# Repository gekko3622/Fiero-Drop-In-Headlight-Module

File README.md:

# 1987-1988 Pontiac Fiero OEM Drop-In Headlight Motor Controller
**PCB Designed by Ryan Blanchard 4.2024**\
**Based On A Project by WalkerTexan**\
**FOR NON-COMMERCIAL USE ONLY.**

**Important:** Please pay attention to the Bill of Materials (BOM). Some components have been changed from my previous designs.\
**This PCB MUST be fabricated with 2 Oz Outer Copper Weight for power handling and safety.**

## Intro

This is a PCB implementation of WalkerTexan's "Fiero Headlight Controller" project.\
I started this project after getting frustrated with the cost and questionable reliability of used modules.\
While there are new reproductions of the original module available, I found the cost to be too high.

After publishing my original PCB implementation, I was challenged to make it fit inside the original GM module's housing. Here it is.

## Repository Contents

**1. Arduino Program**
- WalkerTexan's code for the Arduino Nano.\
This MUST be programmed onto the Pro Micro for the module to function.

**2. Gerber Files (For Production)**
- These are the files that must be provided to a fabricator to produce a PCB.\
  **VERY IMPORTANT:** This PCB MUST be produced with 2 Oz outer copper weight in order to meet power handling requirements.\
  The provided gerber files will produce an identical copy of the PCB installed in my own car, just minus my logo.

  The Zip file can be directly submitted to a fabricator and contains all of the other individual files in this folder.

**3. KiCad Project Files**
- These are my full design schematic and PCB layout files. Use them for learning PCB design or to create your own custom version of the module.

  This project requires KiCad v8 or higher.

## Requirements
This project requires that you already have a fried 87-88 headlight module. (You're considering this project for a reason, right?)\
A Firebird or Corvette module of similar design can also be used.

- You will need to desolder and re-use the original 4 and 5 pin headers from your original module.
- The original module case will also be reused, but requires a single modification.

## Important Building Tips

**1. Arduino Pro Micro**

Due to the low clearance of the GM module casing, the Pro Micro must be installed lower on its pins than standard.\
It is also installed in a DIP socket to further reduce the mounting height.

My recommendation is to install the DIP socket first, then push the Pro Micro's pins into it.\
While installed, push down the plastic spacer, moving side to side until it's as flush as possible with the socket.

You can really see the difference in this side-by-side:

Once you've adjusted the pins for each side, place the Pro Micro onto the pins and solder it while socketed.

**2. Fuses**

I designed the module to directly solder in standard automotive mini fuses.\
For my own board, I used low profile mini fuses in order to avoid having to trim the fuse legs.

Regular mini fuses will work fine, just trim the legs after soldering.
  - 15 amps should be fine assuming your motors are in good shape.

**3. 4/5 Pin Original Header Pins**

The header pins must be installed slightly pulled out from the board to compensate for the added height of the relays.\
I tried my best to capture an image to demonstrate the needed spacing, but it's hard get a clear shot when assembled.

I found it easiest to install the pins one side at a time, getting them lined up right when installed into the housing.\
The holes for the headers are a pretty tight fit, so you should be able to position them fairly easily without them falling out.\
Once I was satisfied with the fitment, I lightly soldered a pin or two per side while still in the casing just to make sure the alignment was right.

**4. Modifying the Module Case**

The sole casing modification needed is to remove most of the plastic spacers from the back panel.\
The plastic is pretty soft, so I was able to grab and twist with vice grips to remove most of the material.

**You do not need to fully remove the spacers, just enough so the back panel can be re-installed without flexing.**\
**The round corner pieces do not need to be removed.**

Here's a comparison of an intact panel and my hastily trimmed panel. If you have the time, sanding them would give a more precise fit.

## Modifications to Original Source
1. Recreated the schematic diagram in KiCad.
2. Designed a PCB based on the schematic.
3. Added fuses and changed the power-on circuit to draw its power from the second 12V source.
4. Substituted the relays for a smaller part with higher current rating.
5. Adapted for compatibility with the original headlight module.

## Credits
The electrical schematic and Arduino code this project is based on were created by WalkerTexan.\
See his original project here: https://www.hackster.io/walkertexan/fiero-headlight-controller-8eaa4c

KiCad Schematic and PCB Layout/Design by Ryan Blanchard.

## License
This project is published under the Creative Commons Attribution-NonCommercial-ShareAlike 4.0 International license.\
Use of this project for commercial purposes is prohibited.

For full details, see the license file.

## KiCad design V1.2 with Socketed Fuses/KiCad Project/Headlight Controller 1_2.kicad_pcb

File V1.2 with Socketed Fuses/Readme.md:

V1.2 maintains the same BOM but adds socketed fuse holders.\
The specific holders I used are the micro fuse holders on this listing:\
https://www.aliexpress.us/item/2255800354773238.html

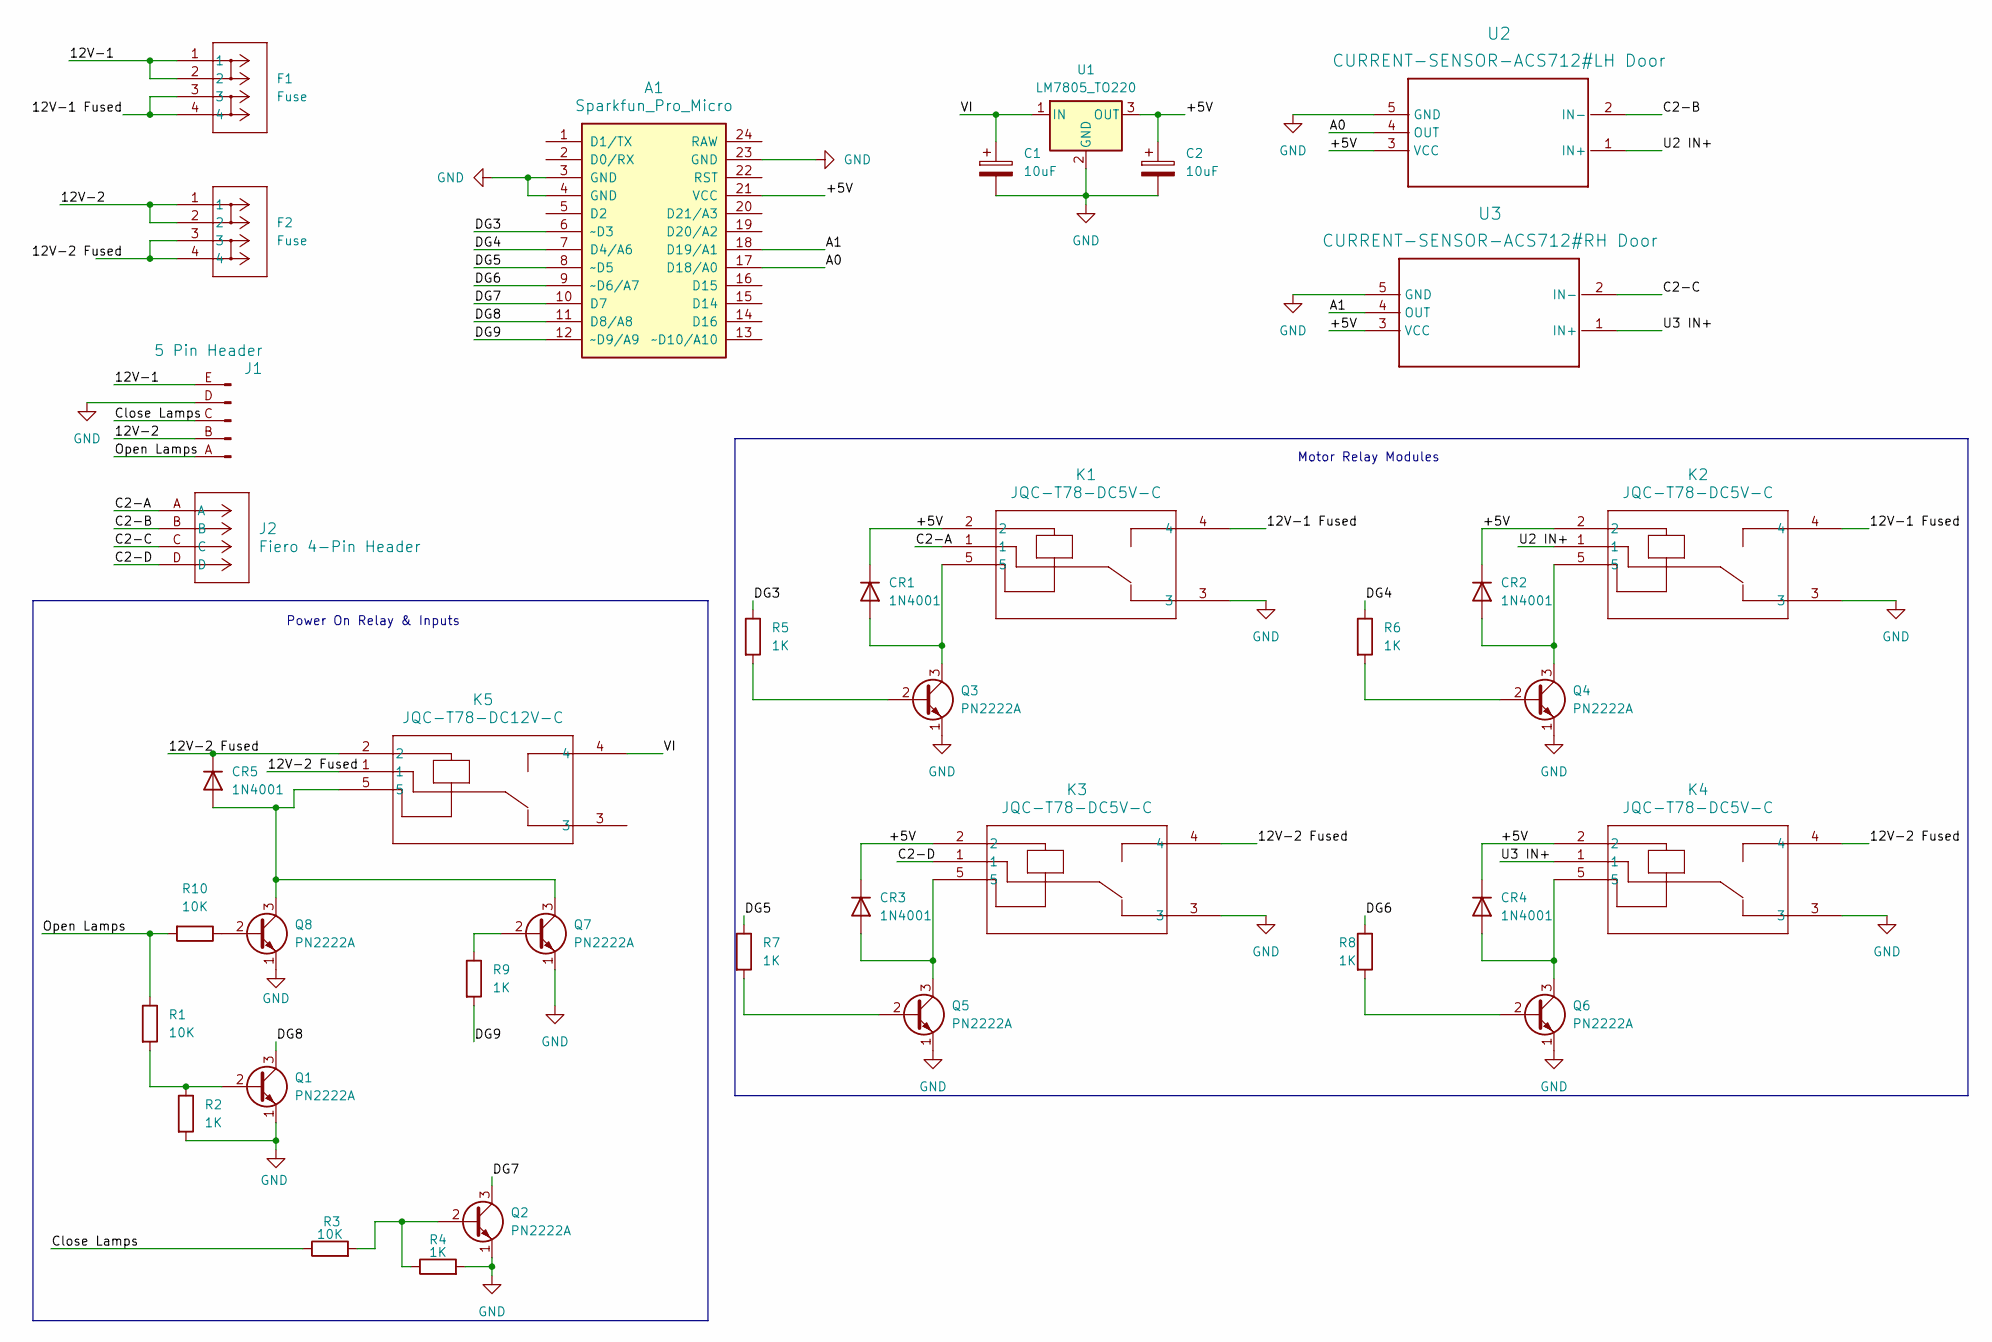
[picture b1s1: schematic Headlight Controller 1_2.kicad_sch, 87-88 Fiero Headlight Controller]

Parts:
A1: Sparkfun_Pro_Micro
C1, C2: 10uF; CAP-TH_BD5.0-P2.00-D0.8-FD
CR1, CR2, CR3, CR4, CR5: 1N4001; DIODE-1N4001
F1, F2: Fuse; LP-Mini Fuse Holder
J1: 5 Pin Header; Fiero Headlight Controller 5-Pin
J2: Fiero 4-Pin Header; Fiero Headlight Controller 4-Pin
K1, K2, K3, K4: JQC-T78-DC5V-C
K5: JQC-T78-DC12V-C; JQC-T78-DC5V-C
Q1, Q2, Q3, Q4, Q5, Q6, Q7, Q8: PN2222A; 2N2222A
R1, R3, R10: 10K; R_Axial_DIN0204_L3.6mm_D1.6mm_P7.62mm_Horizontal
R2, R4, R5, R6, R7, R8, R9: 1K; R_Axial_DIN0204_L3.6mm_D1.6mm_P7.62mm_Horizontal
U1: LM7805_TO220; L7805
U2: CURRENT-SENSOR-ACS712#LH Door; ACS712_A
U3: CURRENT-SENSOR-ACS712#RH Door; ACS712_A

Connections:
/12V-1: F1.1, F1.2, J1.E
/12V-1 Fused: F1.3, F1.4, K1.4, K2.4
/12V-2: F2.1, F2.2, J1.B
/12V-2 Fused: CR5.C (K), F2.3, F2.4, K3.4, K4.4, K5.1, K5.2
/+5V: A1.21 (VCC), C2.1, CR1.C (K), CR2.C (K), CR3.C (K), CR4.C (K), K1.2, K2.2, K3.2, K4.2, U1.3 (OUT), U2.3 (VCC), U3.3 (VCC)
/A0: A1.17 (D18/A0), U2.4 (OUT)
/A1: A1.18 (D19/A1), U3.4 (OUT)
/C2-A: J2.A, K1.1
/C2-B: J2.B, U2.2 (IN-)
/C2-C: J2.C, U3.2 (IN-)
/C2-D: J2.D, K3.1
/Close Lamps: J1.C, R3.1
/DG3: A1.6 (~D3), R5.1
/DG4: A1.7 (D4/A6), R6.1
/DG5: A1.8 (~D5), R7.1
/DG6: A1.9 (~D6/A7), R8.1
/DG7: A1.10 (D7), Q2.3 (C)
/DG8: A1.11 (D8/A8), Q1.3 (C)
/DG9: A1.12 (~D9/A9), R9.2
/Open Lamps: J1.A, R1.1, R10.2
/U2 IN+: K2.1, U2.1 (IN+)
/U3 IN+: K4.1, U3.1 (IN+)
/VI: C1.1, K5.4, U1.1 (IN)
GND: A1.3 (GND), A1.4 (GND), A1.23 (GND), C1.2, C2.2, J1.D, K1.3, K2.3, K3.3, K4.3, Q1.1 (E), Q2.1 (E), Q3.1 (E), Q4.1 (E), Q5.1 (E), Q6.1 (E), Q7.1 (E), Q8.1 (E), R2.2, R4.2, U1.2 (GND), U2.5 (GND), U3.5 (GND)
unnamed: Q1.2 (B), R1.2, R2.1
unnamed: Q2.2 (B), R3.2, R4.1
unnamed: Q3.2 (B), R5.2
unnamed: CR1.A, K1.5, Q3.3 (C)
unnamed: Q4.2 (B), R6.2
unnamed: CR2.A, K2.5, Q4.3 (C)
unnamed: Q5.2 (B), R7.2
unnamed: CR3.A, K3.5, Q5.3 (C)
unnamed: Q6.2 (B), R8.2
unnamed: CR4.A, K4.5, Q6.3 (C)
unnamed: Q7.2 (B), R9.1
unnamed: CR5.A, K5.5, Q7.3 (C), Q8.3 (C)
unnamed: Q8.2 (B), R10.1

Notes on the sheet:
Motor Relay Modules
Power On Relay & Inputs

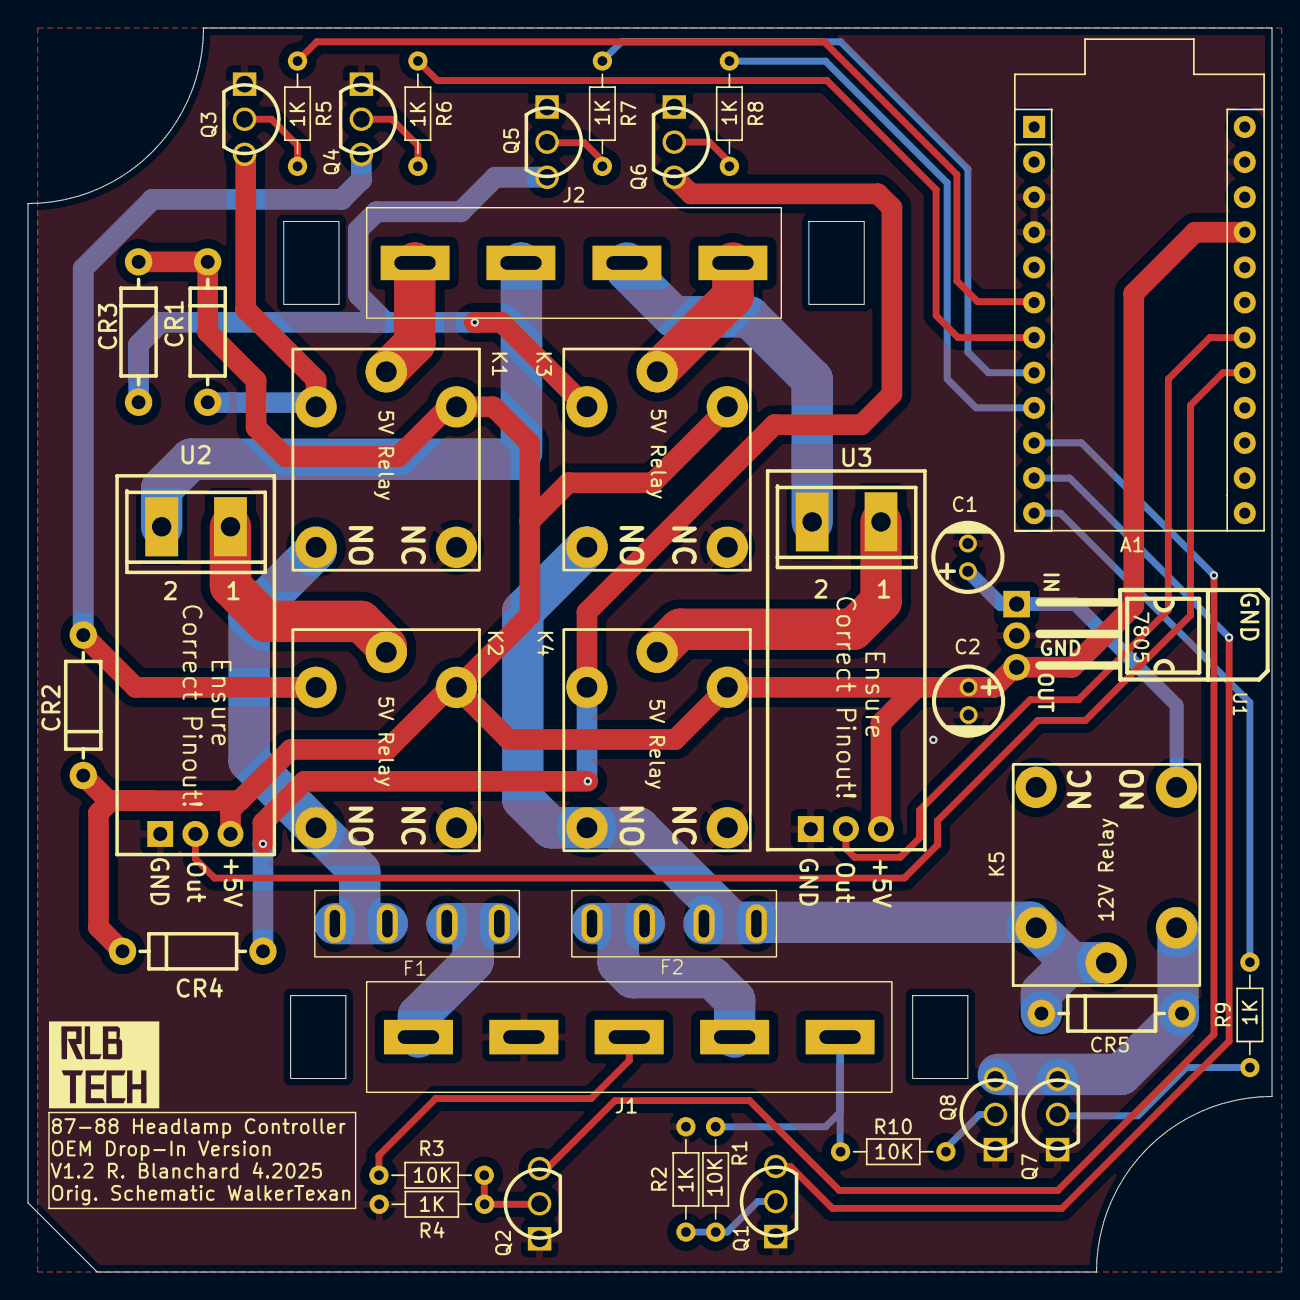
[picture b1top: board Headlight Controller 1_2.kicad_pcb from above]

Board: 2 copper layers, 90.0 x 90.0 mm, 38 parts (0 on the bottom side), 37 nets.

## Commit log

2024-05-09 Add project and gerber files
2024-05-09 Create LICENSE
2024-05-09 Add Arduino Program
2024-05-10 Added pin headers for current sensors
2024-05-11 Fixed a typo
2024-05-11 Update BOM.md
    Forgot to add capacitors previously
2024-05-11 Re-zipped Gerber Files
    Replaced the pre-zipped gerber files as the previous zip archive occasionally gave an error when uploading to JLCPCB.
2024-05-24 Add instructions for special modes
2025-06-14 Add files for v1.2 - added socketed fuse holders
